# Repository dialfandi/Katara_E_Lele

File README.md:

| KATARA  | E-LELE |
| ------ | ----- |
----
# Katara_E_Lele
 This is course project, and my team make iot for to maintenance hydroponic and lcatfish
# Hardware Katara

| **SPESIFICATION** |
| ----- |
----
1. Supply 5-24v
2. Based Microcontroller : ESP32
3. 1 Port of Servo Control
4. 1 Port of PH Sensor
5. 1 Port of LCD i2C
6. 1 Port of Water Temperature
7. 1 Port of Relay Control
----
Author  : Didi Alfandi<br/>
Email   : dialfandi25@gmail.com<br/>
Edited  : 22/12/2020

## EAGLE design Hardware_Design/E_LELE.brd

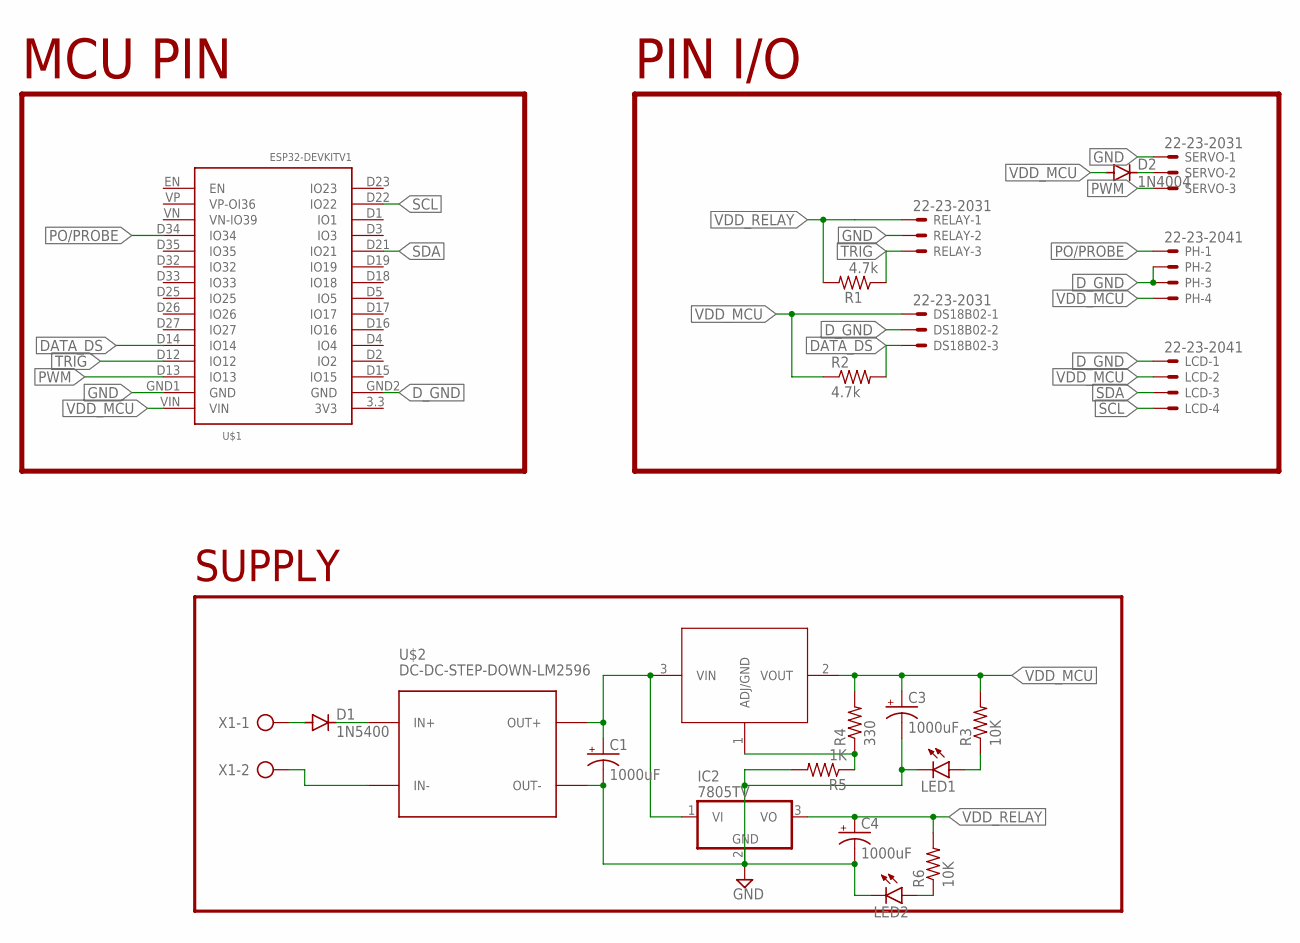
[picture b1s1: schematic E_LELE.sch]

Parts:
C1, C3, C4: 1000uF; E5-10,5
D1: 1N5400; DO201-15
D2: 1N4004; DO41-10
DS18B02: 22-23-2031
IC2: 7805TV; TO220V
LCD: 22-23-2041
LED1, LED2: LED3MM
LM338T: LM1084IT-5.0; T03B_TEX
PH: 22-23-2041
R1, R2: 4.7k; 0204/7
R3, R6: 10K; 0204/7
R4: 330; 0204/7
R5: 1K; 0204/7
RELAY: 22-23-2031
SERVO: 22-23-2031
U$1: ESP32DEVKITV1; ESP32-DEVKITV1
U$2: DC-DC-STEP-DOWN-LM2596
X1: AK500/2

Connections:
ADJ: LM338T.1 (ADJ/GND), R4.1, R5.1
DATA_DS: DS18B02.3, R2.2, U$1.D14 (IO14)
D_GND: DS18B02.2, LCD.1, PH.2, PH.3, U$1.GND2 (GND)
GND: C1.-, C3.-, C4.-, IC2.2 (GND), LED1.K (C), LED2.K (C), R5.2, RELAY.2, SERVO.1, U$1.GND1 (GND), U$2.OUT-
unnamed: D1.A, X1.1
unnamed: D1.C, U$2.IN+
unnamed: U$2.IN-, X1.2
unnamed: LED1.A, R3.1
unnamed: LED2.A, R6.1
OUT+: C1.+, IC2.1 (VI), LM338T.3 (VIN), U$2.OUT+
PO/PROBE: PH.1, U$1.D34 (IO34)
PWM: SERVO.3, U$1.D13 (IO13)
SCL: LCD.4, U$1.D22 (IO22)
SDA: LCD.3, U$1.D21 (IO21)
TRIG: R1.1, RELAY.3, U$1.D12 (IO12)
VDD_MCU: C3.+, D2.A, DS18B02.1, LCD.2, LM338T.2 (VOUT), PH.4, R2.1, R3.2, R4.2, U$1.VIN
VDD_RELAY: C4.+, IC2.3 (VO), R1.2, R6.2, RELAY.1
V_SERVO: D2.C, SERVO.2

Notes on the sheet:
SUPPLY
PIN I/O
MCU PIN

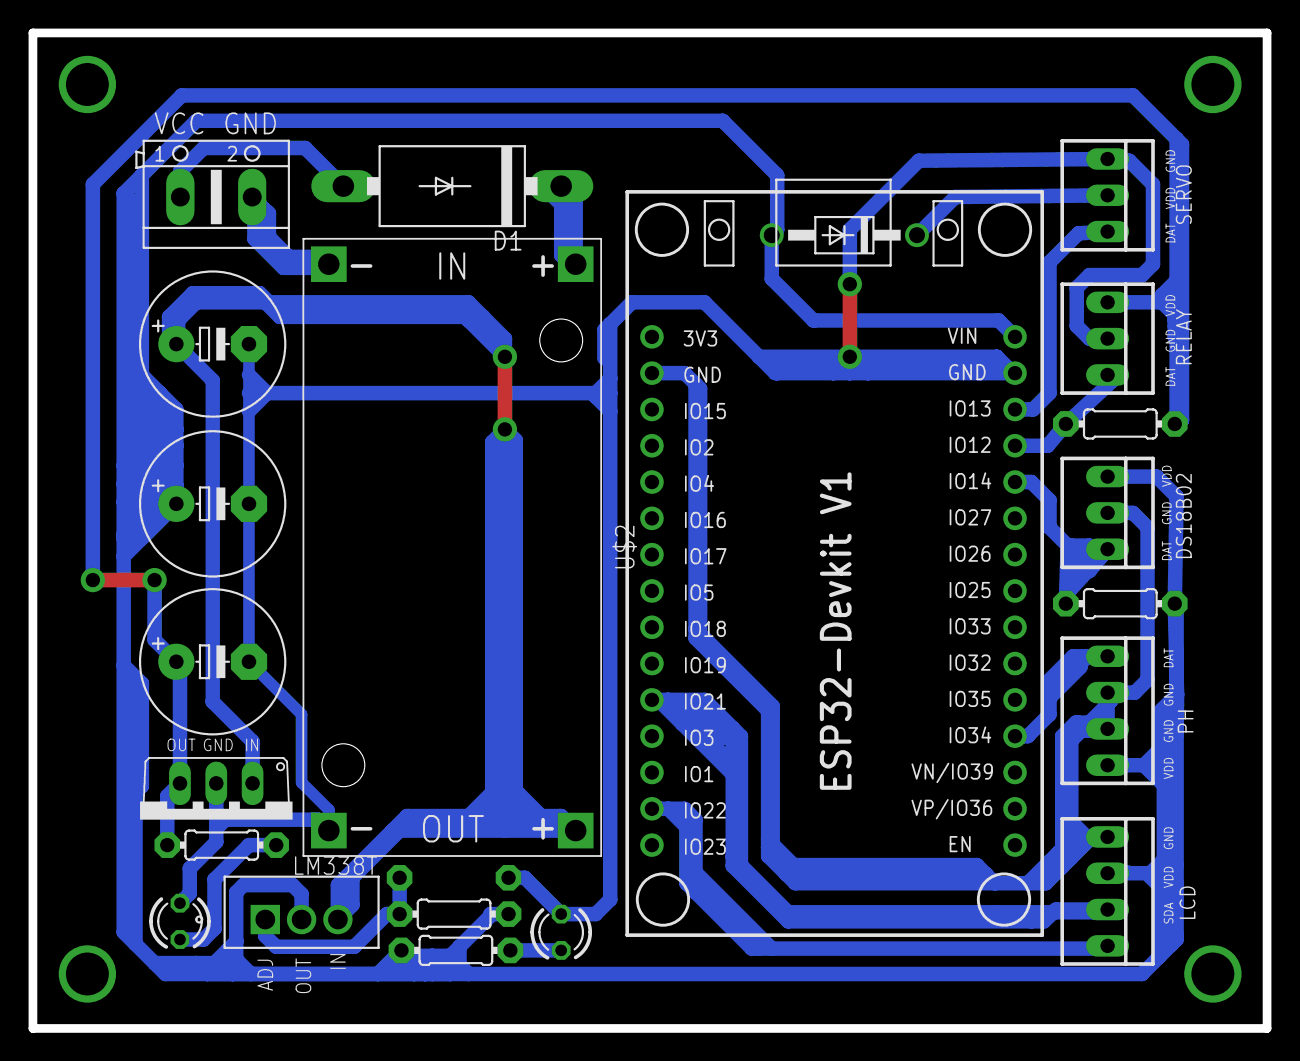
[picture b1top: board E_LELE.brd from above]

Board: 2 copper layers, 86.3 x 69.6 mm, 23 parts (1 on the bottom side), 18 nets.

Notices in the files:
parts and their libraries:
RS485V2: Released under the Creative Commons Attribution 4.0 International License: http://creativecommons.org/licenses/by/4.0
COPYRIGHT: Copyright (C) 2018 Accelerated Designs. All rights reserved
